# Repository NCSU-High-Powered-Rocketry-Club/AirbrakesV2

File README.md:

<div align="center">
<h1 align="center">AirbrakesV2 🚀</h1>
<p align="center">

<b> _Airbrakes deploying on Pelicanator Launch 3_ </b>

</p>

<video src="https://github.com/user-attachments/assets/24dc94fe-5f85-4dfa-9eb1-ef5fc23d2880" autoplay controls loop type="video/mp4"></video>

<b> _Advanced TUI to inspect previous launches_ </b>

<video src="https://github.com/user-attachments/assets/0c72a9eb-0b15-4fbf-9e62-f6a69e5fadaa" autoplay controls loop type="video/mp4"></video>

<b> _A video of our airbrakes extending and retracting_ </b>

</div>

# Table of Contents

- [Overview](#overview)
- [Design](#design)
- [System Architecture Flowchart](#system-architecture-flowchart)
- [Launch Data](#launch-data)
- [File Structure](#file-structure)
- [Quick Start](#quick-start)
- [Local Setup](#local-setup)
  - [1. Clone the repository](#1-clone-the-repository)
  - [2. Install the project](#2-install-the-project)
  - [3. Install the pre-commit hook](#3-install-the-pre-commit-hook)
- [Advanced Local Usage](#advanced-local-usage)
  - [Running Mock Launches](#running-mock-launches)
  - [Running Tests](#running-tests)
  - [Running the Linter](#running-the-linter-and-formatter)
  - [Using the terminal UI](#using-the-terminal-ui)
- [Pi Usage](#pi-usage)
  - [Connecting to the Pi (SSH)](#connecting-to-the-pi-ssh)
  - [Run a real flight with real hardware](#run-a-real-flight-with-real-hardware)
  - [Running Test Scripts](#running-test-scripts)
- [Contributing](#contributing)
- [License](#license)

## Overview
This project is for controlling our air brakes system with the goal of making our rocket "hit" its target apogee. We have a Raspberry Pi 5 as the brains of our system which runs our code. It connects to a servo motor to control the extension of our air brakes and an [IMU](https://www.microstrain.com/inertial-sensors/3dm-cx5-15) (basically an altimeter, accelerometer, and gyroscope). The code follows the [finite state machine](https://www.tutorialspoint.com/design_pattern/state_pattern.htm) design pattern, using the [`AirbrakesContext`](https://github.com/NCSU-High-Powered-Rocketry-Club/AirbrakesV2/blob/main/airbrakes/airbrakes.py) to manage interactions between the states, hardware, logging, and data processing. 

### Design
As per the finite state machine design pattern, we have a context class which links everything together. Every loop, the context:

1. **Gets data from the IMU**
2. **Processes the data** in the Data Processor (calculates velocity, averages, maximums, etc.)
3. **Updates the current state** with the processed data
4. **Predicts the apogee** If the program is in Coast State
5. **Controls the servo extension** based on the current state's instructions (e.g., extends air brakes to slow down the rocket)
6. **Logs all data** from the IMU, Data Processor, Servo, Apogee Predictor and States

### System Architecture Flowchart
```mermaid
%%{init: {'theme': 'dark'}}%%
flowchart TD

    %% Define styles for different shapes
    classDef circular fill:#44007e,stroke:#fff,stroke-width:2px,rx:50%,ry:50%;  %% Ovals for classes
    classDef bubble fill:#164b6c,stroke:#fff,stroke-width:2px,rx:10px,ry:10px; %% Bubbles for methods
    classDef outputSquare fill:#044728,stroke:#fff,stroke-width:2px; %% Squares for outputs
    classDef textStyle fill:none,color:#fff,font-weight:bold,font-size:16px; %% Text style for bold white text
    classDef mainColor fill:#ac6600,stroke:#fff,stroke-width:2px,rx:50%,ry:50%; %% Color for main.py

    %% Main structure with main.py at the top
    subgraph mainFlow[Main Flow]
      direction TB
      mainpy((main.py)):::mainColor --> Airbrakes((Airbrakes Context)):::circular
     
    end
    Airbrakes --> Update[update]:::bubble
    %% IMU Data Packet Flow
    IMUDataPacket --> Update
    Apogee_Predictor --> Update
    
    %% States as individual nodes
    State((State)):::circular
    Standbystate((Standby)):::circular
    MotorBurnState((Motor Burn)):::circular
    CoastState((Coast)):::circular
    FreefallState((Freefall)):::circular
    LandedState((Landed)):::circular

    %% Connections between States and Airbrakes
    State((State)):::circular --> Airbrakes:::circular
    State --> Update
    
    Standbystate((Standby)):::circular --> State
    MotorBurnState((Motor Burn)):::circular --> State
    CoastState((Coast)):::circular --> State
    FreefallState((Freefall)):::circular --> State
    LandedState((Landed)):::circular --> State
    
    %% Connections with Labels
    Airbrakes ---|Child Thread| Logger((Logger)):::circular
    Airbrakes ---|Child Thread| IMU((IMU)):::circular
    Airbrakes ---|Child Thread| Apogee_Predictor((Apogee Predictor)):::circular
    IMU((IMU)):::circular ---|Fetch Packets| IMUDataPacket[(IMU Data Packet)]:::outputSquare

    %% Data Processing
    IMUDataPacket --> DataProcessor[Data Processor]:::circular
    DataProcessor --> Velocity[(Velocity)]:::outputSquare
    DataProcessor --> Altitude[(Altitude)]:::outputSquare
    DataProcessor --> Rotated_Accel[(Rotated Acceleration)]:::outputSquare
    
    Velocity -->  ProcessedData[(Processor Data Packet)]:::outputSquare
    Altitude -->  ProcessedData[(Processor Data Packet)]:::outputSquare
    Rotated_Accel -->  ProcessorData[(Processor Data Packet)]:::outputSquare
    
    ProcessorData[(Processor Data Packet)]:::outputSquare --> Update

    %% Logging Mechanism
    Logger --> LogFunction[log]:::bubble
    Update --> LogData[(Logger Data Packet)]:::outputSquare
    LogData --> LogFunction

    %% Airbrake Control Methods with Parentheses Displayed
    Update --> ExtendAirbrakes[extend_airbrakes]:::bubble
    Update --> RetractAirbrakes[retract_airbrakes]:::bubble

    %% Servo Connections
    RetractAirbrakes --> Servo((Servo)):::circular 
    ExtendAirbrakes --> Servo
    Airbrakes --> Servo

```
| Type        | Color                                                                     | Examples                                                                                                   |
|-------------|---------------------------------------------------------------------------|------------------------------------------------------------------------------------------------------------|
| Entry point |  `#ac6600` | Main.py                                                                                                    |
| Classes     |  `#44007e` | Airbrakes Context, State, Logger, IMU, Data Processor, Servo, Coast, Standby, Freefall, Landed, Motor Burn |
| Methods     |  `#164b6c` | update(), log(), extend_airbrakes(), retract_airbrakes()                                                   |
| Outputs     |  `#044728` | IMU Data Packet, Processor Data Packet, Logger Data Packet                                                 |

### Launch Data

This is our interest launch flight data, altitude over time. The different colors of the line are different states the rocket goes through:
1. Standby - when the rocket is on the rail on the ground.
2. Motor Burn - when the motor is burning and the rocket is accelerating.
3. Coast - after the motor has burned out and the rocket is coasting, this is when air brakes
deployment will be controlled by the bang-bang controller.
4. Free Fall - when the rocket is falling back to the ground after apogee, this is when the air
brakes will be retracted.
5. Landed - when the rocket lands on the ground. After a few seconds in landed state, the
Airbrakes program will end.

### File Structure

We have put great effort into keeping the file structure of this project organized and concise. Try to be intentional on where you place new files or directories.
```
AirbrakesV2/
├── airbrakes/
|   ├── hardware/
│   │   ├── [files related to the connection of the pi with hardware ...]
|   ├── mock/
│   │   ├── [files related to the connection of mock (or simulated) hardware ...]
|   ├── simulation/
│   │   ├── [files related to our custom air brakes sim ...]
|   ├── telemetry/
│   │   ├── [files related to the processing of data ...]
│   ├── [files which control the air brakes at a high level ...]
|   ├── main.py [main file used to run on the rocket]
|   ├── constants.py [file for constants used in the project]
├── tests/  [used for testing all the code]
│   ├── ...
├── logs/  [log files made by the logger]
│   ├── ...
├── launch_data/  [real flight data collected from the rocket]
│   ├── ...
├── scripts/  [small files to test individual components like the servo]
│   ├── ...
├── pyproject.toml [configuration file for the project]
├── README.md
```

## Quick Start

This project only supports Linux. We also strongly recommend using [`uv`](https://docs.astral.sh/uv/) to manage and install
the project. To quickly run the mock replay, simply run:

```bash
uvx --from git+https://github.com/NCSU-High-Powered-Rocketry-Club/AirbrakesV2.git mock
```

You should see the mock replay running with a display!

_Note: We will continue using `uv` for the rest of this README, if you don't want to use `uv`, you can set up the project using Python. See [Legacy Project Setup](legacy_project_setup.md) for more information._

## Local Setup

If you want to contribute to the project, you will need to set up the project locally. Luckily, 
the only other thing you need to install is [`git`](https://git-scm.com/) for version control.

It is highly recommended to use WSL if you are on Windows, as the project only supports Linux. Running natively on Windows should work, but it is not a guarantee.

### 1. Clone the repository:

Run the following in a terminal:
```
git clone https://github.com/NCSU-High-Powered-Rocketry-Club/AirbrakesV2.git

cd AirbrakesV2
```

### 2. Install the project:
```bash
uv self update
uv run mock
```

This will install the project, including development dependencies, activate the virtual environment and run the mock replay.

Potential Issues:
* command 'cc' failed: No such file or directory
  * This means your environment doesn't have a C compiler. Install using:
  ```bash
  sudo apt-get update && sudo apt install -y build-essential
  ```
* Make sure you are on Python 3.14.2 free threaded (`uv python install 3.14.2t`).

_Note: It is important to use `uv run` instead of `uvx` since the `uvx` environment is isolated from
the project. See the [uv documentation](https://docs.astral.sh/uv/concepts/tools/#relationship-to-uv-run) for more information._

_Note 2: The more "correct" command to run is `uv sync`. This will install the project and its dependencies, but not run the mock replay._

### 3. Install the pre-commit hook:
```
uv run prek install
```
This will install a pre-commit hook that will run the linter before you commit your changes.

You will see the linter run now. If one of the checks failed, you can resolve them by following the 
instructions in [Running the Linter](#running-the-linter).

```bash
git push -u origin branch-name
```

## Advanced Local Usage

For performance improvements, we _highly_ recommend switching off the Global Interpreter Lock (GIL),
and turning on the experimental Python Just-In-Time (JIT) compiler. This should be in the `python-settings.env` file, which `uv` will automatically load when you run `uv run ...`.

### Running Mock Launches
Testing our code can be difficult, so we've developed a way to replay previous IMU flight data in real time.

To run a mock launch, run:
```bash
uv run mock
```
If you want to run a mock launch, but with the real servo running, run:
```bash
uv run mock -r
```
There are some additional options you can use when running a mock launch. To view them all, run:
```bash
uv run mock --help
```

### Running Tests
Our CI pipeline uses [pytest](https://pytest.org) to run tests. You can run the tests locally to ensure that your changes are working as expected.

_Note: Unit tests do not work on Windows (only `test_integration.py` will work)._

To run the tests, run this command from the project root directory:
```bash
uv run pytest
```

If your virtual environment is activated, you can simply run the tests with `pytest`

To generate a coverage report from the tests:
```bash
pytest --cov=airbrakes --cov-report=term
```

To performance test the code:
```bash
pytest --benchmark-only --benchmark-save=name
```

See the [pytest-benchmark documentation](https://pytest-benchmark.readthedocs.io/en/stable/) for more information.

To run a performance benchmark with the real IMU on the raspberry pi:
```bash
sudo $(which uv) run pytest -m imu_benchmark
```

Note that the use of `sudo` is required to set process priorities for the main process,
which is critical for accurate benchmarking.

If you make a change to the code, please make sure to update or add the necessary tests.

### Running the Linter and Formatter

Our CI also tries to maintain code quality by running a linter. We use [Ruff](https://docs.astral.sh/ruff/).

To lint and format your code, run:
```bash
uv run prek run --all-files
```

This will run both ruff and doc-formatter.

### Using the terminal UI

An advanced TUI is available under the `term-gui` branch. This UI allows to inspect every flight, including old ones, with much greater detail than the simple text updates. Some features include: 

1. Playing launches at different speeds, including the ability to pause the replay at an instant of time.
2. Viewing the acceleration / velocity / predicted apogee / altitude graphs.
3. A graphical visualization of the rocket
4. Ability to set different target apogees, and view metadata of the flight
5. Automatic application of settings based on the conditions the rocket launched with.
6. Maximum eye candy

```bash
git checkout term-gui && uv run mock
``` 

## Pi Usage

_There are libraries that only fully work when running on the Pi (gpiozero, mscl), so if you're having trouble importing them locally, program the best you can and test your changes on the pi._

### Connecting to the Pi (SSH)
In order to connect to the Pi, you need first to set up a mobile hotspot with the name `HPRC`, password `tacholycos`, and `2.4 GHz` band. Next, turn on the Pi and it will automatically connect to your hotspot. Once it's connected, find the Pi's IP Address, and in your terminal run:
```bash
ssh pi@[IP.ADDRESS]
# Its password is "raspberry"
cd AirbrakesV2/
```

### Install the dependencies needed for the servo integration:

```bash
sudo apt install liblgpio-dev

uv sync --all-extras
```

### Run a real flight with real hardware:
```bash
sudo $(which uv) run real -v
```

### Running Test Scripts
During development, you may want to run individual scripts to test components. For example, to test the servo, run:
```bash
# Make sure you are in the root directory:
uv run scripts/run_servo.py
```

## Contributing
Feel free to submit issues or pull requests. For major changes, please open an issue first to discuss what you would like to change.

## License
This project is licensed under the MIT License. You are free to copy, distribute, and modify the software, provided that the original license notice is included in all copies or substantial portions of the software. See LICENSE for more.

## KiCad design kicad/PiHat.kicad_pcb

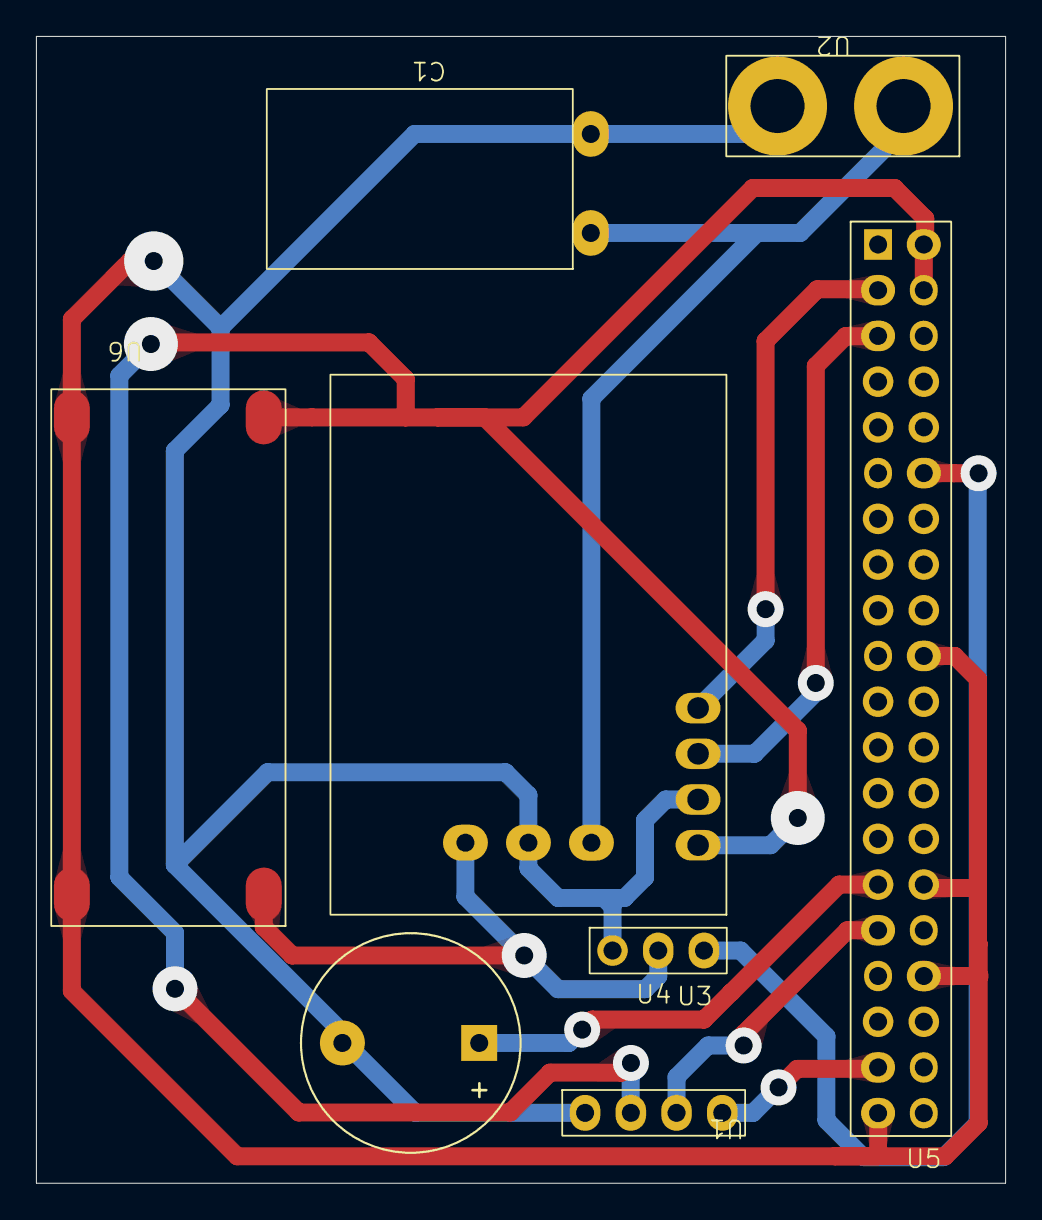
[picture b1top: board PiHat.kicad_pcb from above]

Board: 2 copper layers, 53.8 x 63.7 mm, 8 parts (0 on the bottom side), 9 nets.

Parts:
BZ1: Buzzer; Buzzer_12x9.5RM7.6
C1: 1000u; BigCapacitor
U1: SEN0291; CurrentSensor
U2: Power_Connector; XT60
U3: DS3235; Servo
U4: Encoder
U5: Raspberry_Pi_5; Pi5Hat
U6: UBEC DC/DC Converter; UBEC 5V Step Down

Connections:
+5V: U1.1 (VCC), U4.2 (+), U5.2 (5V_power), U5.4 (5V_power), U6.2 (VOUT)
+7.5V: C1.1, U1.5 (Vin), U1.7 (Vout), U2.1 (Vin), U3.2 (Vin), U6.1 (VIN)
/Buzzer_GPIO: BZ1.1 (+), U5.29 (GPIO_5)
/ENCODER_A: U4.4 (CLK), U5.37 (GPIO_26)
/ENCODER_B: U4.3 (DT), U5.31 (GPIO_6)
/I2C_SCL: U1.3 (SCL), U5.5 (GPIO_3)
/I2C_SDA: U1.4 (SDA), U5.3 (GPIO_2)
/PWM: U3.3 (Signal), U5.12 (GPIO_18)
GND: BZ1.2 (-), C1.2, U1.2 (GND), U1.6 (GND), U2.2 (Ground), U3.1 (GND), U4.1 (GND), U5.6 (Ground), U5.9 (Ground), U5.14 (Ground), U5.20 (Ground), U5.25 (Ground), U5.30 (Ground), U5.34 (Ground), U5.39 (Ground), U6.3 (GND), U6.4 (GND)

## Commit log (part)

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2025-09-20 Zeroed altitude base on averages
2025-09-21 Changed context_data_packet to using state instead of state letter
2025-09-21 Changed context_data_packet to using state type instead of state object
2025-09-21 I can't get the rest of these tests passing
2025-09-21 Fixed the tests
2025-09-21 Fix dumb servo test
2025-09-21 Cleaned up data packets and made servo data packet use the enum for extension
2025-09-21 Do not allow running legacy launch 2
2025-09-21 Got tests passing again
2025-09-21 Got processor data packet stuff half working
2025-09-21 Got almost all the tests passing for the switch to using processor data packets in states
2025-09-21 PR Changes
2025-09-22 Update lockfile
2025-09-22 Make context store information about first pred apogee
2025-09-22 Update tests
2025-10-01 Changed name of method to test_zero_out_altitude. Changed name of variable for buffer. Changed window size to constant. Fixed issues with deque usage in zero_out_altitude. Wrote tests for zero_out_al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
2025-10-12 Initial plan
2025-10-12 Add velocity-based landing detection for soft landings
    - Lowered acceleration threshold from 50 to 30 m/s² based on Huntsville data
    - Added altitude_velocity property to DataProcessor using altitude rate of change
    - Updated FreeFallState to detect landing with low velocity (descending slowly)
    - Added comprehensive tests for velocity-based landing detection
    - All existing tests pass
2025-10-15 Review: No more first apogee pred packet
2025-10-15 self review: Don't use numpy for mean calc's
2025-10-15 Remove todo comment'
2025-10-15 Cleanup
2025-10-15 Remove extra fields in data processor
    This caused the code to run significantly slower
2025-10-17 Only lower acceleration threshold
2025-10-17 Fix no exception being displayed
2025-10-17 Add uv.lock
2025-10-17 Adjust target apogee + metadata update
2025-10-17 Add prelim servo constants
2025-10-18 Improve servo and encoder script
2025-10-18 Made script for bmp
2025-10-18 Fix bug in the servo and encoder script
2025-10-18 Add servo constants
2025-10-21 Add initial pi hat kicad files, wip on schematic and footprints
2025-10-22 Add kicad pcb
2025-10-22 Add footprint for voltage regulator
2025-10-22 Modify pcb for milling a little more. This is the version milled
2025-10-22 Add script for current sensor
2025-10-22 Added current sensor readings to servo interface and telemetry.
2025-10-22 fixed voltage and current fields in LoggerDataPacket and ServoDataPacket test instances.
2025-10-23 change lib
2025-10-31 Change servo angles and extend airbrakes beginning coast
2025-10-31 Comment out tests for no airbrakes control
2025-10-31 Change constants and bump version
2025-10-31 Bump dependencies
2025-10-31 Add import back so tests can pass
2025-11-01 Add government work picture
2025-11-01 Rename jpg
2025-11-01 Actually add the jpg
2025-11-02 Add uv.lock back
2025-11-02 Add government work launch data
2025-11-03 Rename interest launch jpg
2025-11-03 Add renovate.json
2025-11-03 Initial Renovate config
2025-11-03 Move renovate.json5 to .github
2025-11-24 Pin dependencies
2025-11-25 Pin dependencies (#247)
2025-11-25 Update dependency astral-sh/uv to v0.9.11 (#248)
2025-12-01 Got structure for new apogee prediction generally set up
2025-12-01 Made more progress on getting structure right
2025-12-01 Update dependency astral-sh/uv to v0.9.13 (#250)
2025-12-01 Update pre-commit hook astral-sh/ruff-pre-commit to v0.14.7 (#251)
2025-12-02 Fix crash when opening graph for pred apogee
2025-12-02 Add hprm library
2025-12-06 Switch to mscl-rs
2025-12-06 Bump to using Python 3.14
    And remove 3.13 workarounds
2025-12-06 Don't use docformatter in pre-commit
2025-12-06 Remove docformatter from pyproject.toml
2025-12-06 Document needing to install swig for extra dep
2025-12-06 Change target version on ruff
2025-12-06 Add a .python-version
2025-12-07 It's free threaded, baby!
2025-12-07 Use SimpleQueue instead of Queue for perf boost
2025-12-07 Don't make the display hog cpu
    Show process ID as debug info instead
2025-12-07 Update tests to work with ft
2025-12-08 Update pre-commit hook python-jsonschema/check-jsonschema to v0.35.0 (#256)
2025-12-08 Add source for polars ft wheels
2025-12-08 Update actions/checkout action to v6 (#257)
2025-12-08 Test: try specifying schema length for arm64 issue
2025-12-08 Change url for arm64 polars-runtime-32
2025-12-08 Enforce Python 3.14.2t with .python-version
2025-12-08 Revert
2025-12-08 Switched to multithreading
2025-12-08 Bump mscl-rs to 0.2.0
2025-12-09 Remove workaround for schema inference
2025-12-09 Fix CI
2025-12-09 Fix CI take 2
2025-12-09 Fix CI take 3
2025-12-10 Integrated hprm into apogee predictor
2025-12-10 Updated fields in apogee predictor packets
2025-12-10 a lil bit of this and that
2025-12-10 update display
2025-12-12 Got old tests (except integration tests) passing
2025-12-12 Fixed integration tests and finished apogee_predictor tests
2025-12-13 Fix apogee prediction bug
2025-12-13 Updated hprm version and servo angles
2025-12-13 Make MockIMU use flight's parameters in apg pred
2025-12-13 Copilot Review: Fix field name
2025-12-13 Switch on airbrakes control, rename govt work file, add metadata
2025-12-14 Removed sim from tests
2025-12-14 Update workflows now that we're public again
2025-12-14 silly polars
2025-12-15 [pre-commit.ci] pre-commit autoupdate
    updates:
    - [github.com/astral-sh/ruff-pre-commit: v0.14.8 → v0.14.9](https://github.com/astral-sh/ruff-pre-commit/compare/v0.14.8...v0.14.9)
    - [github.com/python-jsonschema/check-jsonschema: 0.35.0 → 0.36.0](https://github.com/python-jsonschema/check-jsonschema/compare/0.35.0...0.36.0)
2025-12-17 Add parameter estimation
2025-12-22 [pre-commit.ci] pre-commit autoupdate
    updates:
    - [github.com/astral-sh/ruff-pre-commit: v0.14.9 → v0.14.10](https://github.com/astral-sh/ruff-pre-commit/compare/v0.14.9...v0.14.10)
2026-01-12 [pre-commit.ci] pre-commit autoupdate
    updates:
    - [github.com/astral-sh/ruff-pre-commit: v0.14.10 → v0.14.11](https://github.com/astral-sh/ruff-pre-commit/compare/v0.14.10...v0.14.11)
2026-01-15 started adding firm
2026-01-15 Added cc issue to readme
2026-01-16 decent changes
2026-01-19 [pre-commit.ci] pre-commit autoupdate
    updates:
    - [github.com/astral-sh/ruff-pre-commit: v0.14.11 → v0.14.13](https://github.com/astral-sh/ruff-pre-commit/compare/v0.14.11...v0.14.13)
2026-01-20 added changes for data proccesor and context
2026-01-22 [pre-commit.ci] auto fixes from pre-commit.com hooks
    for more information, see https://pre-commit.ci
2026-01-26 bump hprm version
2026-01-26 [pre-commit.ci] pre-commit autoupdate
    updates:
    - [github.com/astral-sh/ruff-pre-commit: v0.14.13 → v0.14.14](https://github.com/astral-sh/ruff-pre-commit/compare/v0.14.13...v0.14.14)
    - [github.com/python-jsonschema/check-jsonschema: 0.36.0 → 0.36.1](https://github.com/python-jsonschema/check-jsonschema/compare/0.36.0...0.36.1)
2026-02-01 Converted more of the code to using FIRM
2026-02-01 update the logger and main for firm
2026-02-01 added code for pretend firm
2026-02-01 Update metadata for govt work 2 scrubbed
2026-02-02 Switch to using prek instead of pre-commit
2026-02-02 Add action to run prek on CI
2026-02-02 Reenable docformatter, ruff fixes
2026-02-02 Remove unneeded dependency
2026-02-02 moved log files, added script, and fix data processor
2026-02-02 Refactored a lot of unit tests
2026-02-03 Refactored even more of the tests
2026-02-03 Bump polars to 1.37.1, add windows to ci
2026-02-04 Got some more of the tests passing
2026-02-04 Did a first pass of MockFIRM and got some more tests passing
2026-02-04 fixed unit tests in state and context. only 1 issue left in context is IdleFirm doesn't have a queue method. Still 20 errors left
2026-02-05 got more tests passing
2026-02-05 Deleted processor_data_packet and fixed even more tests
2026-02-05 Got mock working?
2026-02-06 Fix mock and add plot script
2026-02-06 Fixed display
2026-02-06 fixed polars
2026-02-06 Made get_data_packets block
2026-02-06 update constants
2026-02-07 did some more work for firm
2026-02-07 Switch to govt work 2 launch config
2026-02-07 Bump to version 3.0
2026-02-07 Change target to 1600ft
2026-02-07 Make extra plot script
2026-02-08 add script for plotting old imu data
2026-02-09 Add govt work 2 data
2026-02-09 Clarify why we didn't hit the target apogee
2026-02-09 Fix pitch calc test
2026-02-09 Update README with videos and formatting changes
    Added videos and enhanced README structure.
2026-02-09 Re-encode tui video to mp4
2026-02-10 changed servo and base servo
2026-02-14 Added changes to Servo and base servo incase read functions do not end up wokring. Also changed mock servo and some unit tests.
2026-02-16 updated servo and mock servo to use @property and fixed unit tests except some issue with gpio0 and firm
2026-02-20 removed encoder
2026-02-20 Servo constants
2026-02-20 add script for calibration
2026-02-20 Change constants again
2026-02-21 Modify pretend launch data file with new kalman filter tuning
2026-02-21 Do my review comments, fix tests
2026-02-21 add calibration scripts
2026-02-21 Update state logic and metadata for flight
2026-02-21 Fix prek
2026-02-21 Change servo deploy logic
2026-02-22 Fix mock firm, add jackpot 1, fix tests
2026-02-22 Remove comment
2026-02-22 Fix windows test
2026-02-28 Add current sensor, update TUI script
2026-02-28 Bump uv version in CI
2026-02-28 Use the smbus2 branch for pi-ina219
2026-02-28 Try to keep windows support
2026-02-28 Change log buffer size to match 5 seconds FIRM data
2026-02-28 Remove benchmark workflow
2026-03-02 Update actions/checkout digest to de0fac2
2026-03-02 Pin j178/prek-action action to 0bb87d7
2026-03-02 Add back pitch calculation, show target apogee in display
2026-03-03 Add max and min current values to graph
2026-03-03 Poll current sensor every 0.1ms
2026-03-06 Add voltage reading to TUI
2026-03-10 Apply suggestion from @JacksonElia
2026-03-11 Data processor changes
2026-03-11 whoops forgot to change the name
2026-03-11 context and state changes
2026-03-11 fixed unit test errors. just waiting on derived_raw_acceleration_z_gs from firm client.
2026-03-12 Add start and stop method to servo
2026-03-12 data processor and apogee prediction updates. Still getting same results for both types of altitudes
2026-03-13 fixed stuff
2026-03-13 Got unit tests passing
2026-03-13 updated constants
2026-03-13 updated constants and fixed ruff
2026-03-13 added firm log file
2026-03-13 added in hardcode logic
2026-03-13 airbrakes extensions
2026-03-13 Update metadata for jack 2
2026-03-16 Added jackpot 2 metadata
2026-03-16 changed metadata schema to be more FIRM-oriented
2026-03-16 forgot to add the length
2026-03-16 Fixed tests, cleaned up meta data, and added motor
2026-03-22 removed imu launches
2026-03-22 updated firm data packet fields and logging
2026-03-25 pr changes and lowered landed detection accel
2026-03-25 Added firm launches
2026-03-26 fixed failing tests
2026-03-27 oops accidentally deleted launch
2026-03-27 fixed failing test
2026-03-27 added gyro cal script
2026-03-31 Added meta data for firm pretends
2026-04-01 Disallow packages newer than last 7 days
2026-04-05 Add jackpot launch 3 data
2026-04-05 Update launch data
2026-04-13 Update actions/setup-python action to v6
2026-04-13 Update astral-sh/setup-uv action to v8
2026-04-13 Update j178/prek-action action to v2
2026-04-14 Update dependency pytest to v9.0.3 [SECURITY]
2026-04-15 adjust max_extension and max_no_buzz
2026-04-15 fixed error to pass tests
2026-04-17 fixed meta data weight. Fixed firm issue with headers
2026-04-17 made it wait a bit after retracting to switch
2026-04-17 Added jackpot_3 airbrakes firm log and added current sensor to display
2026-04-17 unit test for switch to pressure delay
2026-04-17 ruff fixes
2026-04-18 Add control of servo switch for Airbender v0.3
2026-04-18 Copilot Review: Release line, linux only dep
2026-04-19 Update servo constants (full deployment)
2026-04-19 day before launch
2026-04-24 final measurements
2026-04-24 measurment
2026-04-27 Lock file maintenance
2026-05-15 Update j178/prek-action action to v2 (#320)
2026-06-01 Make test less flakey
2026-06-10 refactored servo, baseservo, mockservo classes
